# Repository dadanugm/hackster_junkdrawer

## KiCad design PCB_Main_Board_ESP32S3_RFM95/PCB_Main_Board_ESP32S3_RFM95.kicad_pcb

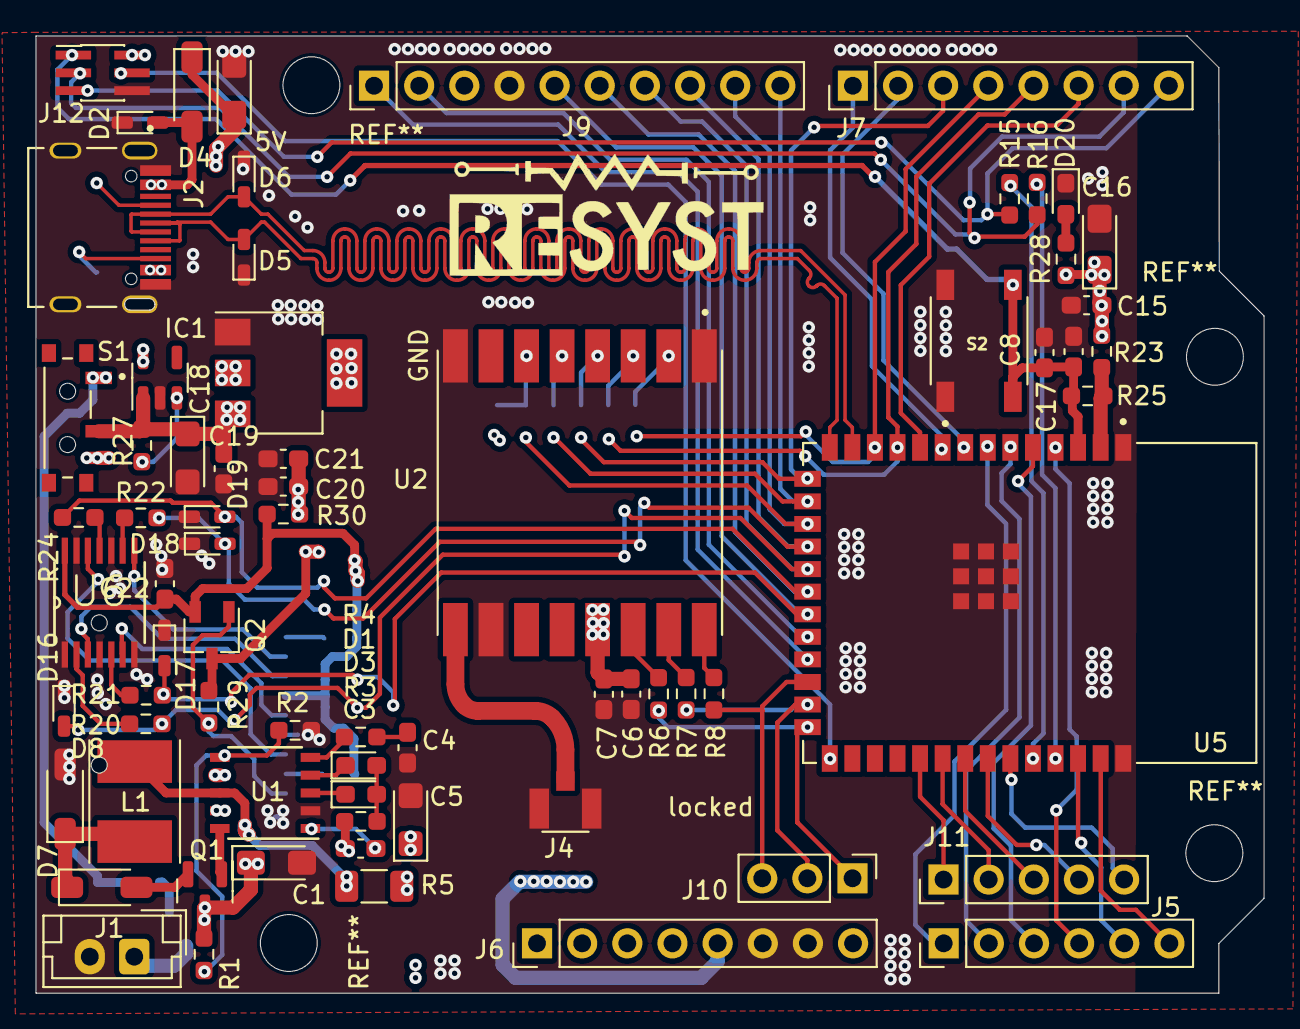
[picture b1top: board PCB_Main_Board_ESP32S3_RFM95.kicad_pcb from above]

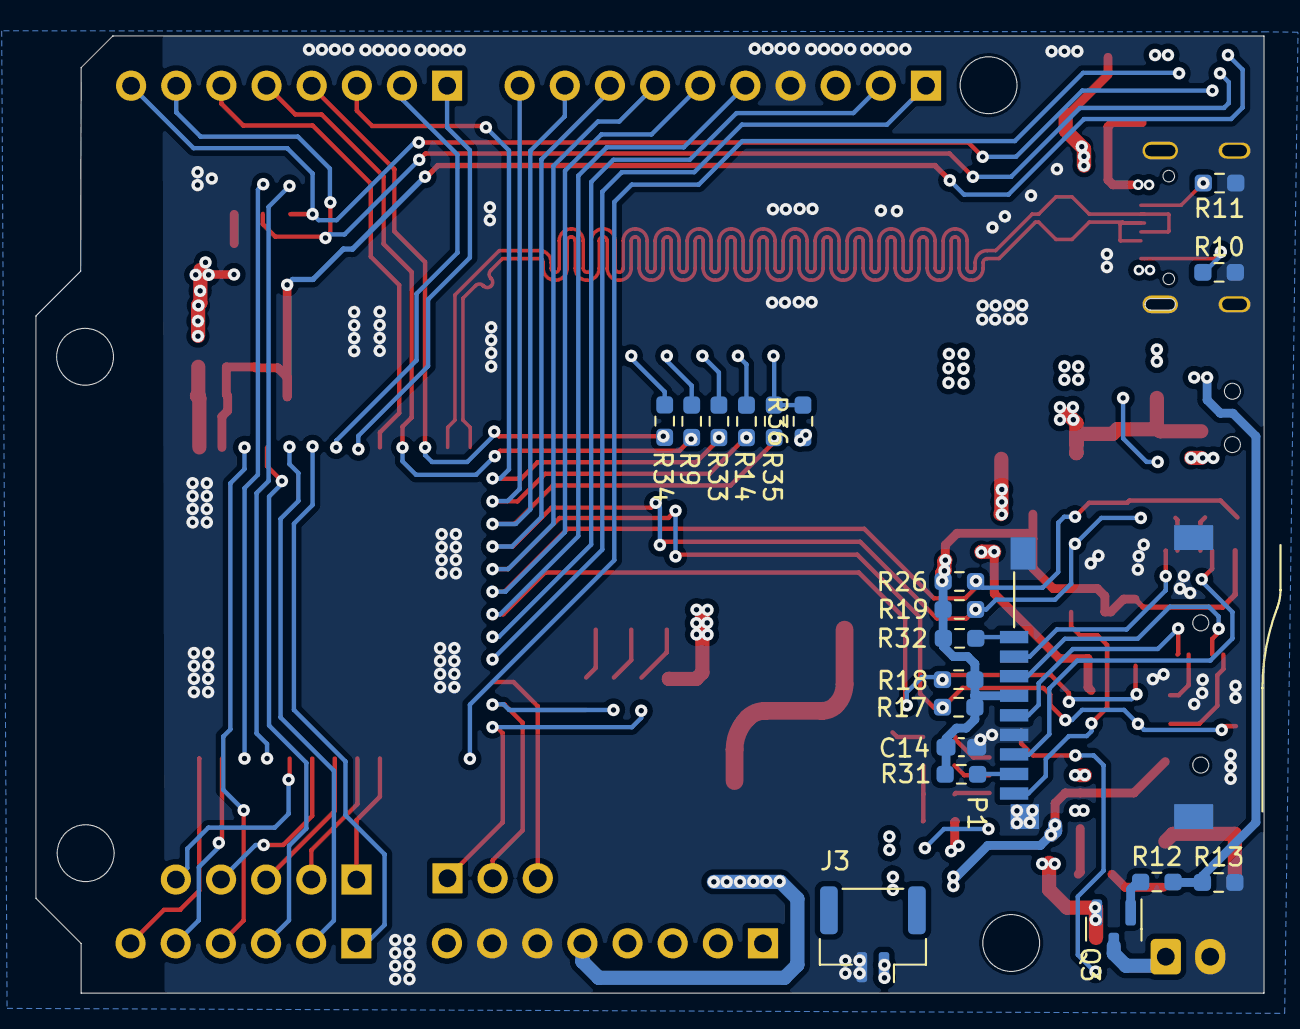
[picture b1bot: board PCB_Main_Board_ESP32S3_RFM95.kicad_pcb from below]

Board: 4 copper layers, 69.1 x 53.8 mm, 90 parts (20 on the bottom side), 81 nets.

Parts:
C1: 10uF; CP_EIA-3216-18_Kemet-A_Pad1.58x1.35mm_HandSolder
C2, C16: 10uF/25V Tantalum; CP_EIA-3216-18_Kemet-A_Pad1.58x1.35mm_HandSolder
C3, C4, C6, C8, C14, C15, C21, C22: 100nf; C_0603_1608Metric_Pad1.08x0.95mm_HandSolder
C5: 1uF; CP_EIA-3216-18_Kemet-A
C7: 1uf; C_0603_1608Metric_Pad1.08x0.95mm_HandSolder
C17: 1uF; C_0603_1608Metric_Pad1.08x0.95mm_HandSolder
C18: CP1; CP_EIA-3216-18_Kemet-A
C19, C20: 470pf; C_0603_1608Metric_Pad1.08x0.95mm_HandSolder
D1, D3, D20: LED; LED_0603_1608Metric_Pad1.05x0.95mm_HandSolder
D2, D5, D6: LESD5D5.0CT1G; D_SOD-523
D4, D7, D8: 1N5819WS; D_SOD-123
D16, D17, D18, D19: D_TVS; D_SOD-523
IC1: ME6211; SOT-23-5
J1: Conn_01x02_Male; JST_EH_B2B-EH-A_1x02_P2.50mm_Vertical
J2: USB-C; USB-C-2
J3: Conn_01x02_Male; JST_GH_SM02B-GHS-TB_1x02-1MP_P1.25mm_Horizontal
J4: UFL; UFL_CONN
J5: Analog_Pin; PinHeader_1x06_P2.54mm_Vertical
J6: Power_Pin; PinHeader_1x08_P2.54mm_Vertical
J7: Dig_Pin_0-7; PinHeader_1x08_P2.54mm_Vertical
J9: Dig_Pin_8-18; PinHeader_1x10_P2.54mm_Vertical
J10: Conn_01x03; PinHeader_1x03_P2.54mm_Vertical
J11: Conn_01x05_Pin; PinHeader_1x05_P2.54mm_Vertical
J12: Conn_02x03_Odd_Even; PinHeader_2x03_P1.00mm_Vertical_SMD
L1: L; L_Taiyo-Yuden_NR-50xx_HandSoldering
P1: MICRO_SD_Socket; MicroSD_Footprints
Q1: Q_PNP_BEC; SOT-23
Q2: Q_PMOS_GDS; TSOT-23
Q3: AO3401A; SOT-23
R1, R12, R13, R17, R18, R19, R25, R26, R36: 10K; R_0603_1608Metric_Pad0.98x0.95mm_HandSolder
R2, R3, R6, R7, R8, R9, R10, R11, R14, R20, R21, R22, R24, R33, R34, R35: 3.3K; R_0603_1608Metric_Pad0.98x0.95mm_HandSolder
R4: 120; R_0603_1608Metric_Pad0.98x0.95mm_HandSolder
R5: RS 50; R_1206_3216Metric_Pad1.30x1.75mm_HandSolder
R15, R16, R28: 22; R_0603_1608Metric_Pad0.98x0.95mm_HandSolder
R23: 0; R_0603_1608Metric_Pad0.98x0.95mm_HandSolder
R27: 1M; R_0603_1608Metric_Pad0.98x0.95mm_HandSolder
R29, R31, R32: 10k; R_0603_1608Metric_Pad0.98x0.95mm_HandSolder
R30: NM/BYPASS; R_0603_1608Metric_Pad0.98x0.95mm_HandSolder
S1: EG1215AA; SW_Slide_SPST_Side
S2: SW_Tactile
U1: CN3791; SSOP-10_3.9x4.9mm_P1.00mm
U2: RFM95W; RFM95
U5: ESP32-S3-WROOM-1-N8R8; ESP32S3_WROOM_1N8R8
U6: 74LVC125A
U7: SGM2212; SOT-223-3_TabPin2

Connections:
/5V: C2.1, D4.1 (K), R12.2, R13.1, S1.1
/ESP32S3_Minsys/3V3: C6.2, C7.2, C15.2, C16.1, C20.2, C21.2, IC1.5 (VOUT), J6.4, J12.2, Q2.3 (S), R23.2, R28.1, R29.1, R30.1, R36.1, U2.13 (3.3V), U7.2 (VO)
/ESP32S3_Minsys/ANT: J4.3 (SIG), U2.9 (ANT)
/ESP32S3_Minsys/CHIP_PU: C8.1, C17.2, J12.1, R25.1, S2.3, S2.4, U5.3 (EN)
/ESP32S3_Minsys/ESP_3V3: R23.1, R25.2, U5.2 (3V3)
/ESP32S3_Minsys/ESP_RXD: J7.8, J12.5, R15.1
/ESP32S3_Minsys/ESP_TXD: J7.7, J12.3, R16.1
/ESP32S3_Minsys/GPIO_0: J12.4, U5.27 (IO0)
/ESP32S3_Minsys/GPIO_38: J11.1, U5.31 (IO38)
/ESP32S3_Minsys/IO3/D5: J7.3, R33.2, U5.15 (IO3)
/ESP32S3_Minsys/IO4/A5: J5.6, U5.39 (IO1)
/ESP32S3_Minsys/IO5/A4: J5.5, U5.38 (IO2)
/ESP32S3_Minsys/IO6/A3: J5.4, U5.4 (IO4)
/ESP32S3_Minsys/IO7/A2: J5.3, U5.5 (IO5)
/ESP32S3_Minsys/IO8/D4: J7.4, R34.2, U5.12 (IO8)
/ESP32S3_Minsys/IO9/D9: J9.9, R35.2, U5.17 (IO9)
/ESP32S3_Minsys/IO10/D10: D18.2 (A2), J9.8, R19.2, R22.2, U5.18 (IO10)
/ESP32S3_Minsys/IO11/D11/ESP_MOSI: D16.2 (A2), J9.7, R17.2, R20.2, U5.19 (IO11)
/ESP32S3_Minsys/IO12/D12/ESP_MISO: D19.2 (A2), J9.6, R24.2, R26.2, U5.20 (IO12)
/ESP32S3_Minsys/IO13/D13/ESP_SCK: D17.2 (A2), J9.5, R18.2, R21.2, U5.21 (IO13)
/ESP32S3_Minsys/IO14/D14/ESP_I2C_SDA: J9.2, U5.22 (IO14)
/ESP32S3_Minsys/IO15: J7.2, U5.8 (IO15)
/ESP32S3_Minsys/IO15/A1: J5.2, U5.6 (IO6)
/ESP32S3_Minsys/IO15/D15/ESP_I2C_SCL: J9.1, U5.23 (IO21)
/ESP32S3_Minsys/IO16: J7.1, U5.9 (IO16)
/ESP32S3_Minsys/IO16/A0: J5.1, U5.7 (IO7)
/ESP32S3_Minsys/IO17/D2: J7.6, U5.10 (IO17)
/ESP32S3_Minsys/IO18/D3: J7.5, R9.1, U5.11 (IO18)
/ESP32S3_Minsys/IO39: J11.2, U5.32 (IO39)
/ESP32S3_Minsys/IO40: J11.3, U5.33 (IO40)
/ESP32S3_Minsys/IO41: J11.4, U5.34 (IO41)
/ESP32S3_Minsys/IO42: J11.5, U5.35 (IO42)
/ESP32S3_Minsys/IO45: J10.1, R6.2, U5.26 (IO45)
/ESP32S3_Minsys/IO46/D8: J9.10, R14.2, U5.16 (IO46)
/ESP32S3_Minsys/IO47: J10.3, R8.2, U5.24 (IO47)
/ESP32S3_Minsys/IO48: J10.2, R7.2, U5.25 (IO48)
/ESP32S3_Minsys/RST_RFM: R35.1, R36.2, U2.6 (RESET)
/ESP32S3_Minsys/SD_DET: P1.9 (CD), Q2.1 (G), R29.2
/ESP32S3_Minsys/SD_VCC: C14.2, C22.2, P1.4 (VDD), Q2.2 (D), R17.1, R18.1, R19.1, R26.1, R30.2, R31.1, R32.1, U6.14 (VCC)
/ESP32S3_Minsys/SPI_CLK: P1.5 (SPI_CLK), U6.6 (2Y)
/ESP32S3_Minsys/SPI_CS: P1.2 (SPI_CS), U6.8 (3Y)
/ESP32S3_Minsys/SPI_MISO: P1.7 (SPI_MISO), U6.12 (4A)
/ESP32S3_Minsys/SPI_MOSI: P1.3 (SPI_MOSI), U6.3 (1Y)
/U1_N: D6.2 (A2), J2.A7 (DN1), J2.B7 (DN2), U5.13 (IO19)
/U1_P: D5.2 (A2), J2.A6 (DP1), J2.B6 (DP2), U5.14 (IO20)
/VBAT: C5.1, J3.1, R5.1, S1.3, U1.7 (BAT)
/VBUS: C1.1, C3.1, D2.2 (A2), D4.2 (A), J2.A4 (VBUS_A), J2.A9 (VBUS_A), J2.B4 (VBUS_B), J2.B9 (VBUS_B), Q1.3 (C), Q3.2 (S), R1.1, R3.1, U1.9 (VCC)
/VIN: C18.1, C19.2, IC1.1 (VIN), J6.5, R27.2, S1.2, U7.3 (VI)
GND: C1.2, C2.2, C4.2, C5.2, C6.1, C7.1, C8.2, C14.1, C15.1, C16.2, C17.1, C18.2, C19.1, C20.1, C21.1, C22.1, D2.1 (A1), D5.1 (A1), D6.1 (A1), D8.2 (A), D16.1 (A1), D17.1 (A1), D18.1 (A1), D19.1 (A1), D20.1 (K), IC1.2 (GND), J1.2, J2.A1 (GND_A), J2.A12 (GND_A), J2.B1 (GND_B), J2.B12 (GND_B), J2.S1 (SHELL_GND), J2.S2 (SHELL_GND), J2.S3 (SHELL_GND), J2.S4 (SHELL_GND), J3.2, J4.1 (GND), J4.2 (GND), J6.6, J6.7, J9.4, J12.6, P1.6 (GND), P1.G1 (GND), P1.G2 (GND), P1.G3 (GND), P1.G4 (GND), R2.2, R10.2, R11.1, R13.2, S2.1, S2.2, U1.2 (GND), U2.1 (GND), U2.8 (GND), U2.10 (GND), U5.1 (GND), U5.40 (GND), U5.41_1 (GND), U5.41_2 (GND), U5.41_3 (GND), U5.41_4 (GND), U5.41_5 (GND), U5.41_6 (GND), U5.41_7 (GND), U5.41_8 (GND), U5.41_9 (GND), U6.1 (1~OE), U6.4 (2~OE), U6.7 (GND), U6.10 (3~OE), U6.13 (4~OE), U7.1 (ADJ)
unnamed: C4.1, R4.1
unnamed: D1.2 (A), D3.2 (A), R3.2
unnamed: D1.1 (K), U1.4 (DONE)
unnamed: D3.1 (K), U1.3 (CHRG)
unnamed: D7.2 (A), Q1.2 (E)
unnamed: D7.1 (K), D8.1 (K), L1.1
unnamed: D20.2 (A), R28.2
unnamed: IC1.3 (CE), R27.1
unnamed: J1.1, Q3.3 (D)
unnamed: J2.A5 (CC1), R11.2
unnamed: J2.B5 (CC2), R10.1
unnamed: P1.8 (DAT1), R31.2
unnamed: P1.1 (DAT2), R32.2
unnamed: Q1.1 (B), U1.10 (DRV)
unnamed: Q3.1 (G), R12.1
unnamed: R4.2, U1.5 (COM)
unnamed: L1.2, R5.2, U1.8 (CSP)
unnamed: R1.2, R2.1, U1.6 (MPPT)
unnamed: C3.2, U1.1 (VG)
unnamed: R6.1, U2.14 (DIO0)
unnamed: R7.1, U2.15 (DIO1)
unnamed: R8.1, U2.16 (DIO2)
unnamed: R34.1, U2.2 (MISO)
unnamed: R9.2, U2.3 (MOSI)
unnamed: R14.1, U2.5 (NSS)
unnamed: R33.1, U2.4 (SCK)
unnamed: R15.2, U5.36 (RXD0)
unnamed: R16.2, U5.37 (TXD0)
unnamed: R20.1, U6.2 (1A)
unnamed: R21.1, U6.5 (2A)
unnamed: R22.1, U6.9 (3A)
unnamed: R24.1, U6.11 (4Y)
